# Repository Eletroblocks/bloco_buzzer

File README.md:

# buzzer
Utiliza a energia elétrica recebida para produzir SOM.

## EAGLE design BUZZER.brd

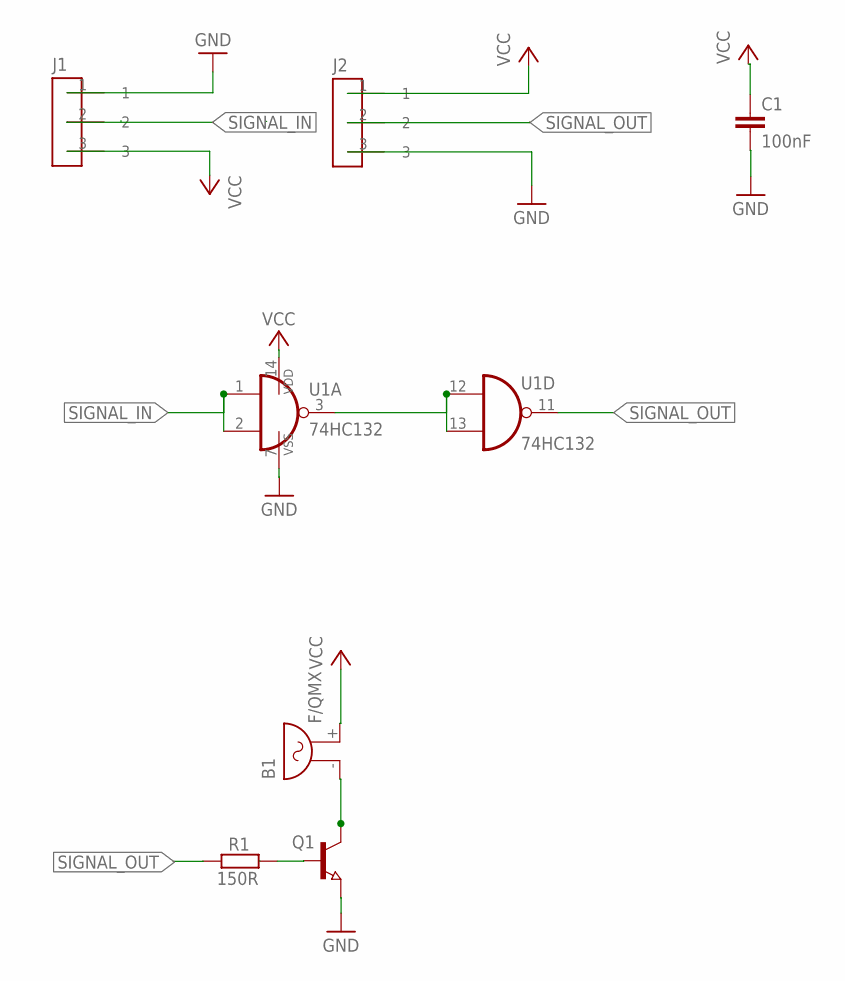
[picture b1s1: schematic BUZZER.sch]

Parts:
B1: F/QMX
C1: 100nF; C0805
J1: CONECTOR_MACHO; MALE
J2: CONECTOR_FEMEA; FEMALE
Q1: BC817; SOT23
R1: 150R; R0805W
U1: 74HC132; SO14

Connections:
GND: C1.2, J1.1, J2.3, Q1.2 (E), U1.7 (VSS)
unnamed: U1.3 (O), U1.12 (I0), U1.13 (I1)
unnamed: Q1.1 (B), R1.1
unnamed: B1.- (1), Q1.3 (C)
SIGNAL_IN: J1.2, U1.1 (I0), U1.2 (I1)
SIGNAL_OUT: J2.2, R1.2, U1.11 (O)
VCC: B1.+ (2), C1.1, J1.3, J2.1, U1.14 (VDD)

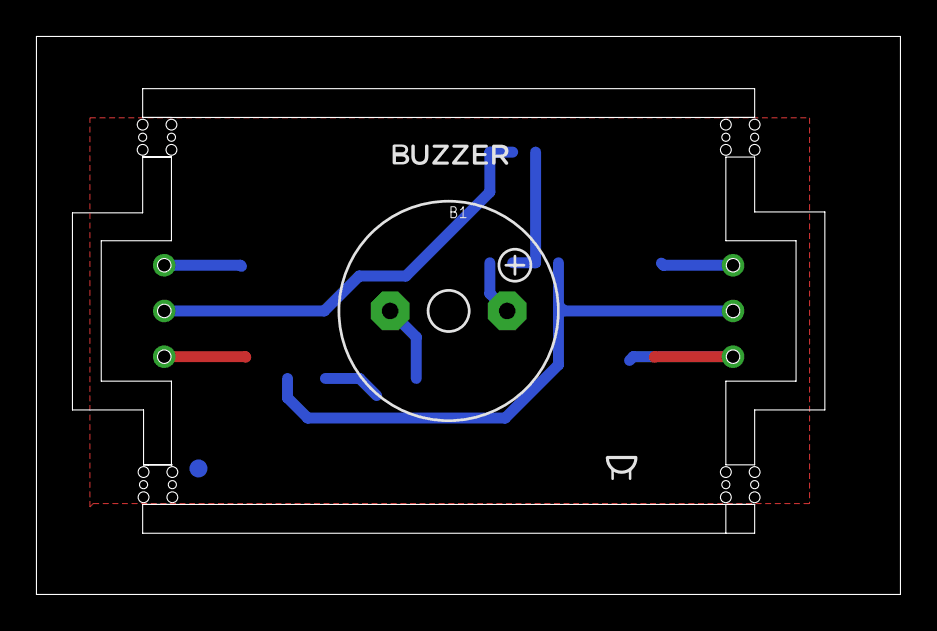
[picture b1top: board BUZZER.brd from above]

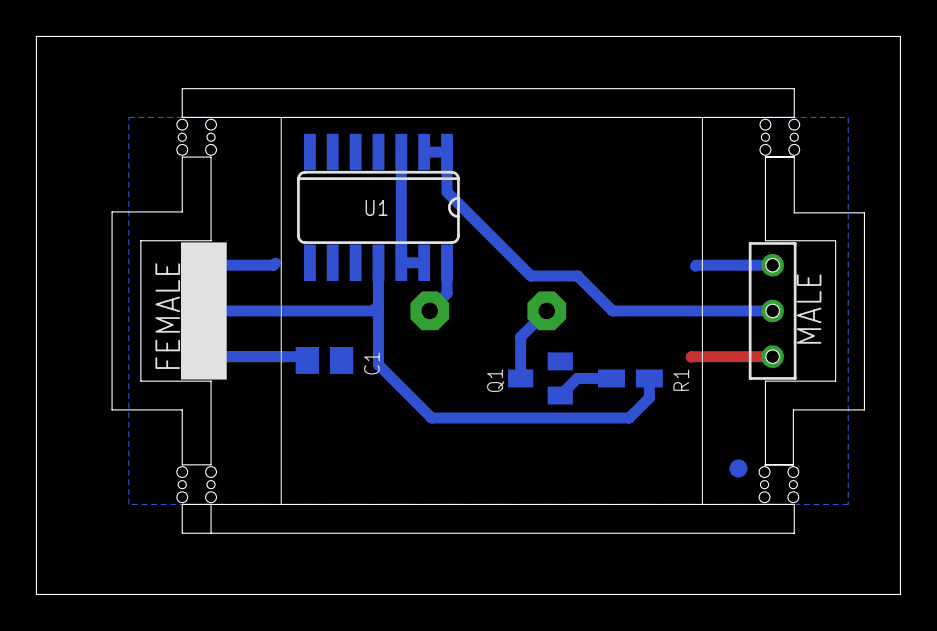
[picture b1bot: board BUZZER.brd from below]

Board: 2 copper layers, 48.0 x 31.0 mm, 12 parts (5 on the bottom side), 7 nets.

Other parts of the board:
U$1: FIDUCIAL_G10
U$2, U$3, U$4, U$5: STAMP_DUPLO

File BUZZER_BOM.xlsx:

BOM LIST BUZZER
DESCRIPTION | QUANTITY | POSITION | PART NUMBER
RESISTOR 150R. 0805 | 1 | R1 | CRGH0805J150R, can be replaced to similar
CAPACITOR 100nF 0805 | 1 | C1 | UMF212B7104KGHT, can be replaced to similar
TRANSISTOR BC817 | 1 | Q1 | BC817K-16HR, can be replaced to similar
NAND SHCMITT TRIGGER | 1 | U1 | 74HC132D,653
BUZZER 5V | 1 | B1 | CMI-1295-0585T
MALE CONNECTOR | 1 | J1 | THIS COMPONENT IS PROVIDE BY ELETROBLOCKS
FEMALE CONNECTOR | 1 | J2 | THIS COMPONENT IS PROVIDE BY ELETROBLOCKS

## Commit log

2020-11-16 init project
2020-11-17 correção de pads e adição de label para versionamento
2020-11-17 Rename .gitigore to .gitignore
2020-11-17 deletando arquivos inuteis
2020-11-17 deletando aquivos inuteis
2020-11-23 correção de label
2020-12-28 organizando arquivos
2020-12-28 imagem
2021-03-10 V1.0.3

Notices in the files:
parts and their libraries:
dicons: Copyright (C) 2004, Bob Starr (rtzaudio@mindspring.com)
